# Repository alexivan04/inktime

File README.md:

# InkTime – Open Source Smartwatch Hardware Project

## Overview
InkTime is an open-source, low-cost smartwatch hardware platform designed for mass production.  
This repository contains the complete hardware, manufacturing, and mechanical design files for the device.

The project includes:
- electronic schematic and PCB layout
- manufacturing outputs (Gerber, BOM, Pick & Place)
- complete 3D mechanical assembly
- documentation and design decisions
- validation and review updates

## Repository Structure

```text
InkTime/
│
├── Hardware/
│   ├── inktime.sch
│   ├── inktime.brd
│   └── schematic.pdf
│
├── Manufacturing/
│   ├── gerbers.zip
│   ├── bom.csv
│   └── pick_and_place.csv
│
├── Mechanical/
│   ├── inktime_assembly.step
│   └── inktime_assembly.f3d
│
├── Images/
│   ├── pcb_top.png
│   ├── pcb_bottom.png
│   ├── render_front.png
│   └── exploded_view.png
│
├── LICENSE
└── README.md
````

---

## Block Diagram

```text
Battery
   │
   ▼
Power Management (charger + regulation)
   │
   ▼
nRF52840 Microcontroller
   ├── IMU Sensor (I2C / SPI)
   ├── E-paper Display (SPI)
   ├── Buttons (GPIO)
   ├── USB-C Interface
   ├── Vibration Motor / Shaker
   └── Debug / Test Pads
```

---

## Hardware Architecture

The smartwatch is built around the **nRF52840** microcontroller, selected for:

* low power consumption
* integrated BLE support
* sufficient GPIO availability
* embedded ARM Cortex-M4 core

### Main Modules

* **Microcontroller:** nRF52840
* **Display:** e-paper display connected via SPI
* **Motion Sensor:** IMU connected via I2C/SPI
* **Power Supply:** Li-Po battery with charging IC and voltage regulation
* **User Input:** 3 push buttons
* **Feedback:** vibration motor (shaker)
* **Communication:** USB-C + BLE
* **Programming/Test:** dedicated test pads

---

## PCB Design Notes

### Stack-up

* **4-layer PCB**
* components placed **TOP layer only**
* routing on both TOP and BOTTOM
* GND planes on 1 and 3 layers

### Routing Rules

* power traces: **0.30 mm**
* signal traces: **minimum 0.15 mm**
* no right-angle routing
* minimized vias on power lines
* decoupling capacitors placed near IC supply pins

### RF Requirements

* antenna positioned at PCB edge
* no copper under antenna
* no signal traces below antenna
* board cutout included below antenna region

---

## Mechanical Integration

The PCB is designed to fit inside the provided smartwatch enclosure.

## Design Decisions / Notes

* accepted minor dimension warnings for button and USB alignment per project instructions
* battery connected directly to test pads to save internal volume
* all decoupling capacitors placed as close as possible to supply pins
* RF section isolated with stitched ground vias

---

## License

This project is released under the **Apache 2.0 License**.

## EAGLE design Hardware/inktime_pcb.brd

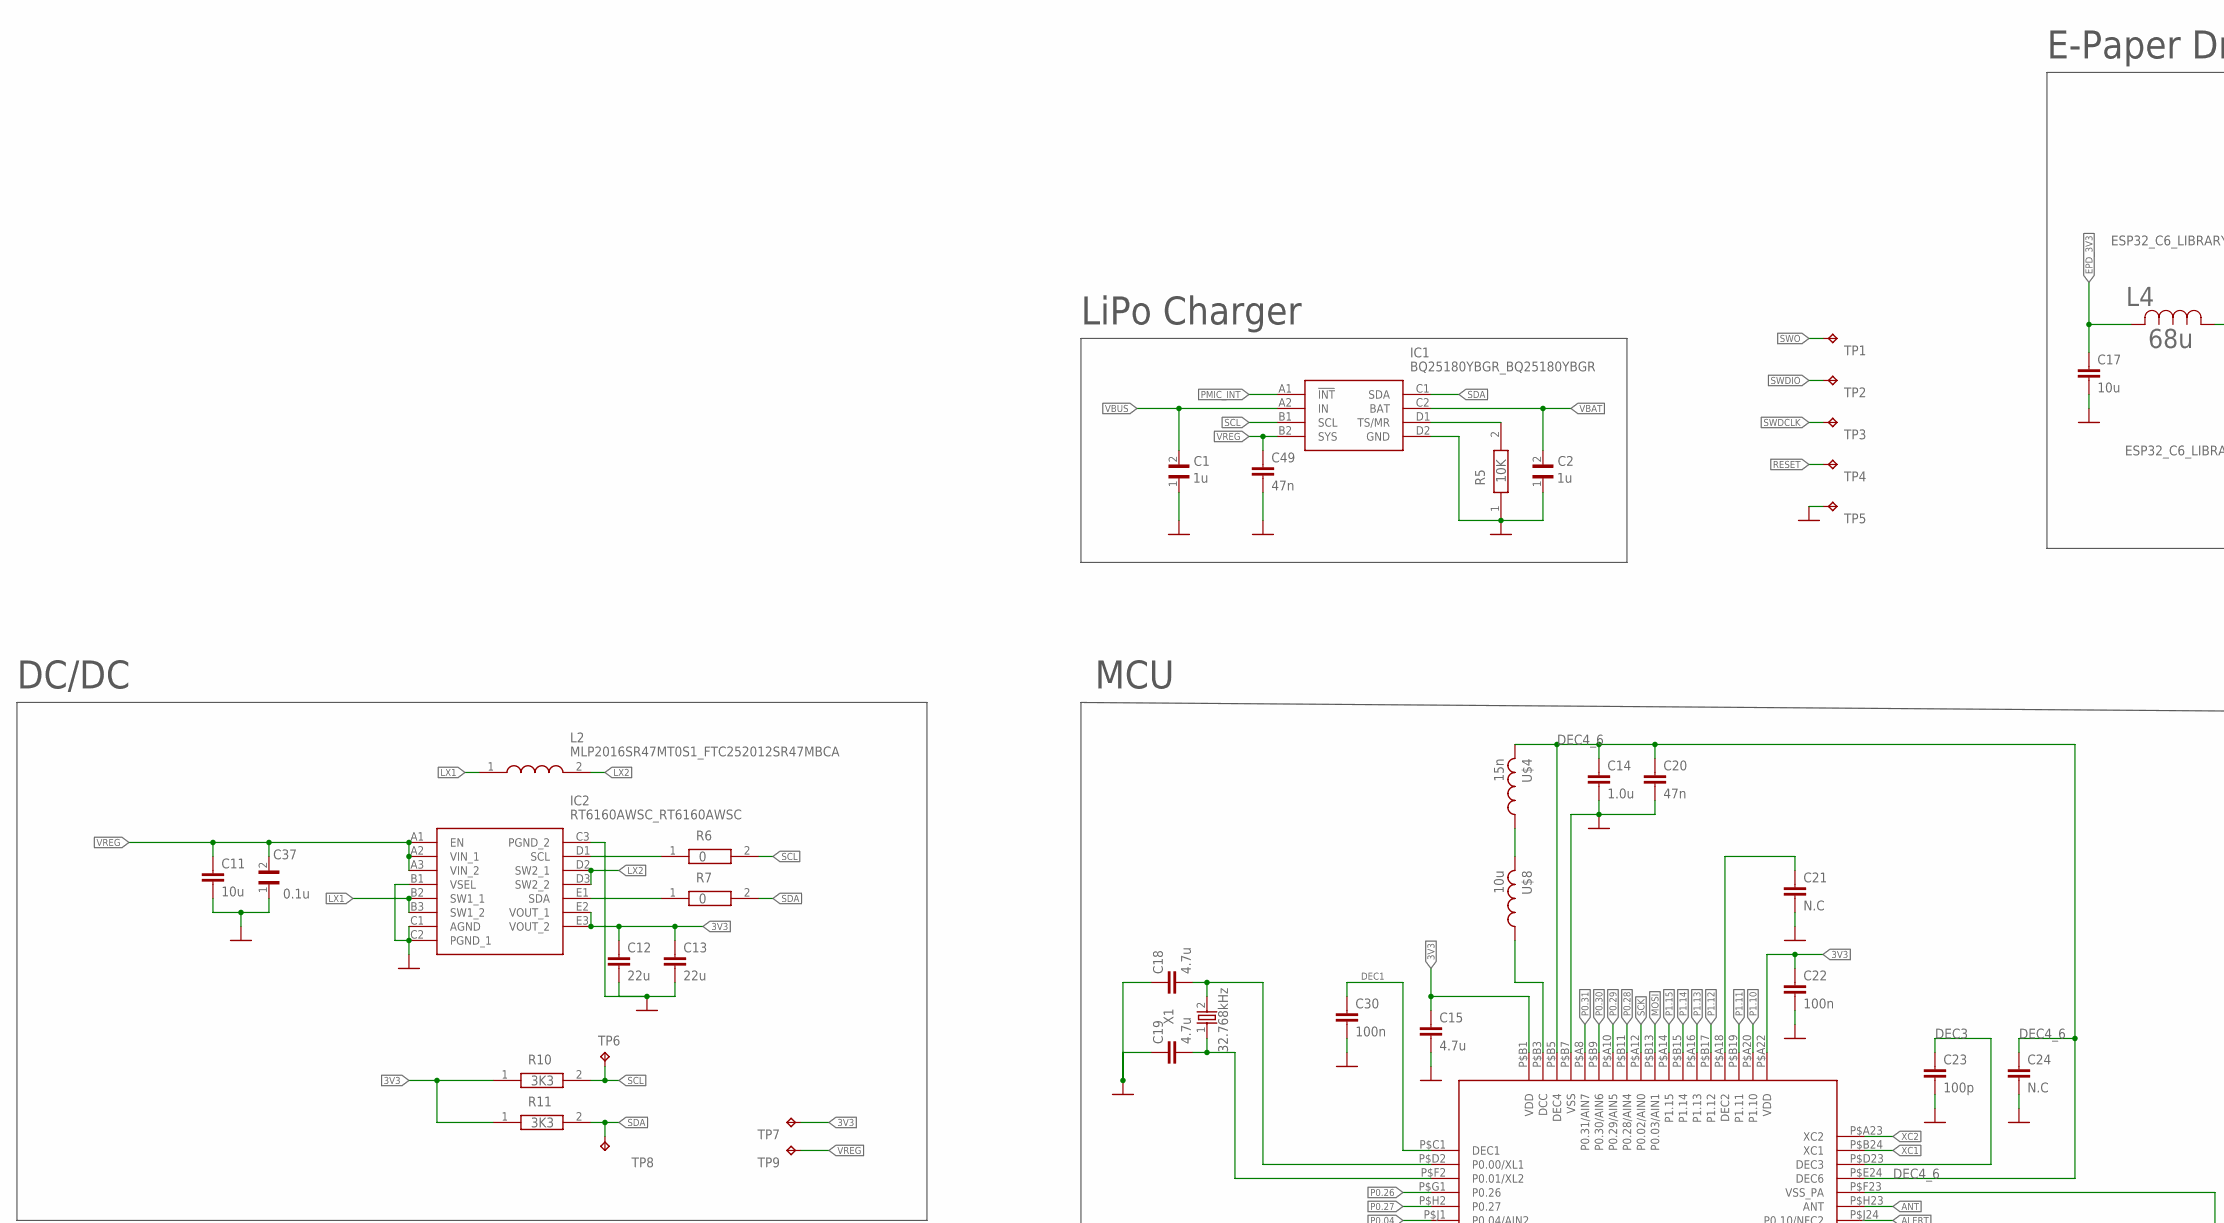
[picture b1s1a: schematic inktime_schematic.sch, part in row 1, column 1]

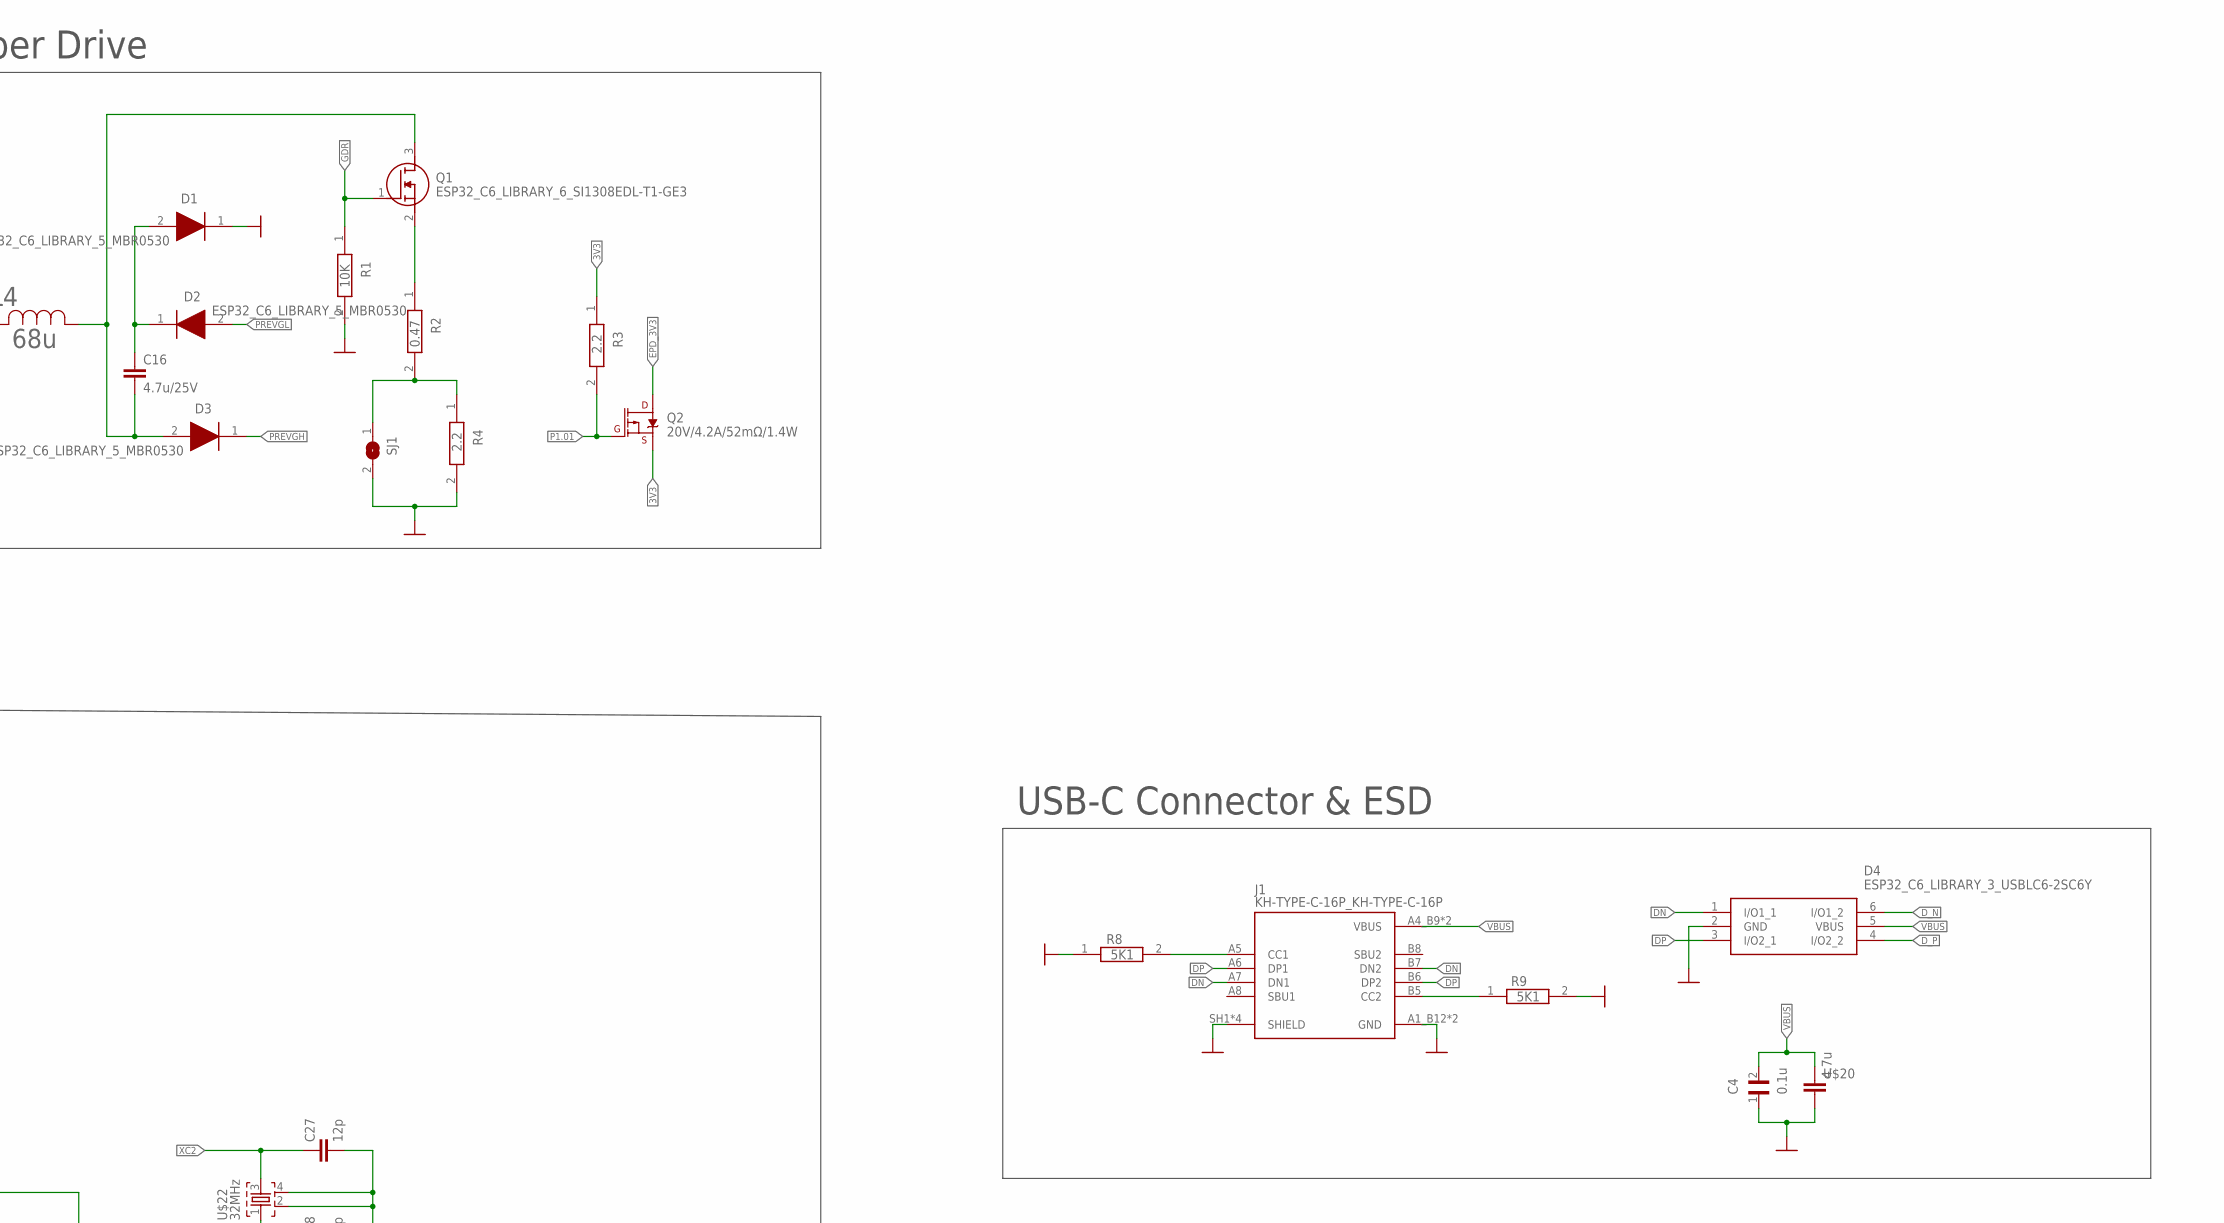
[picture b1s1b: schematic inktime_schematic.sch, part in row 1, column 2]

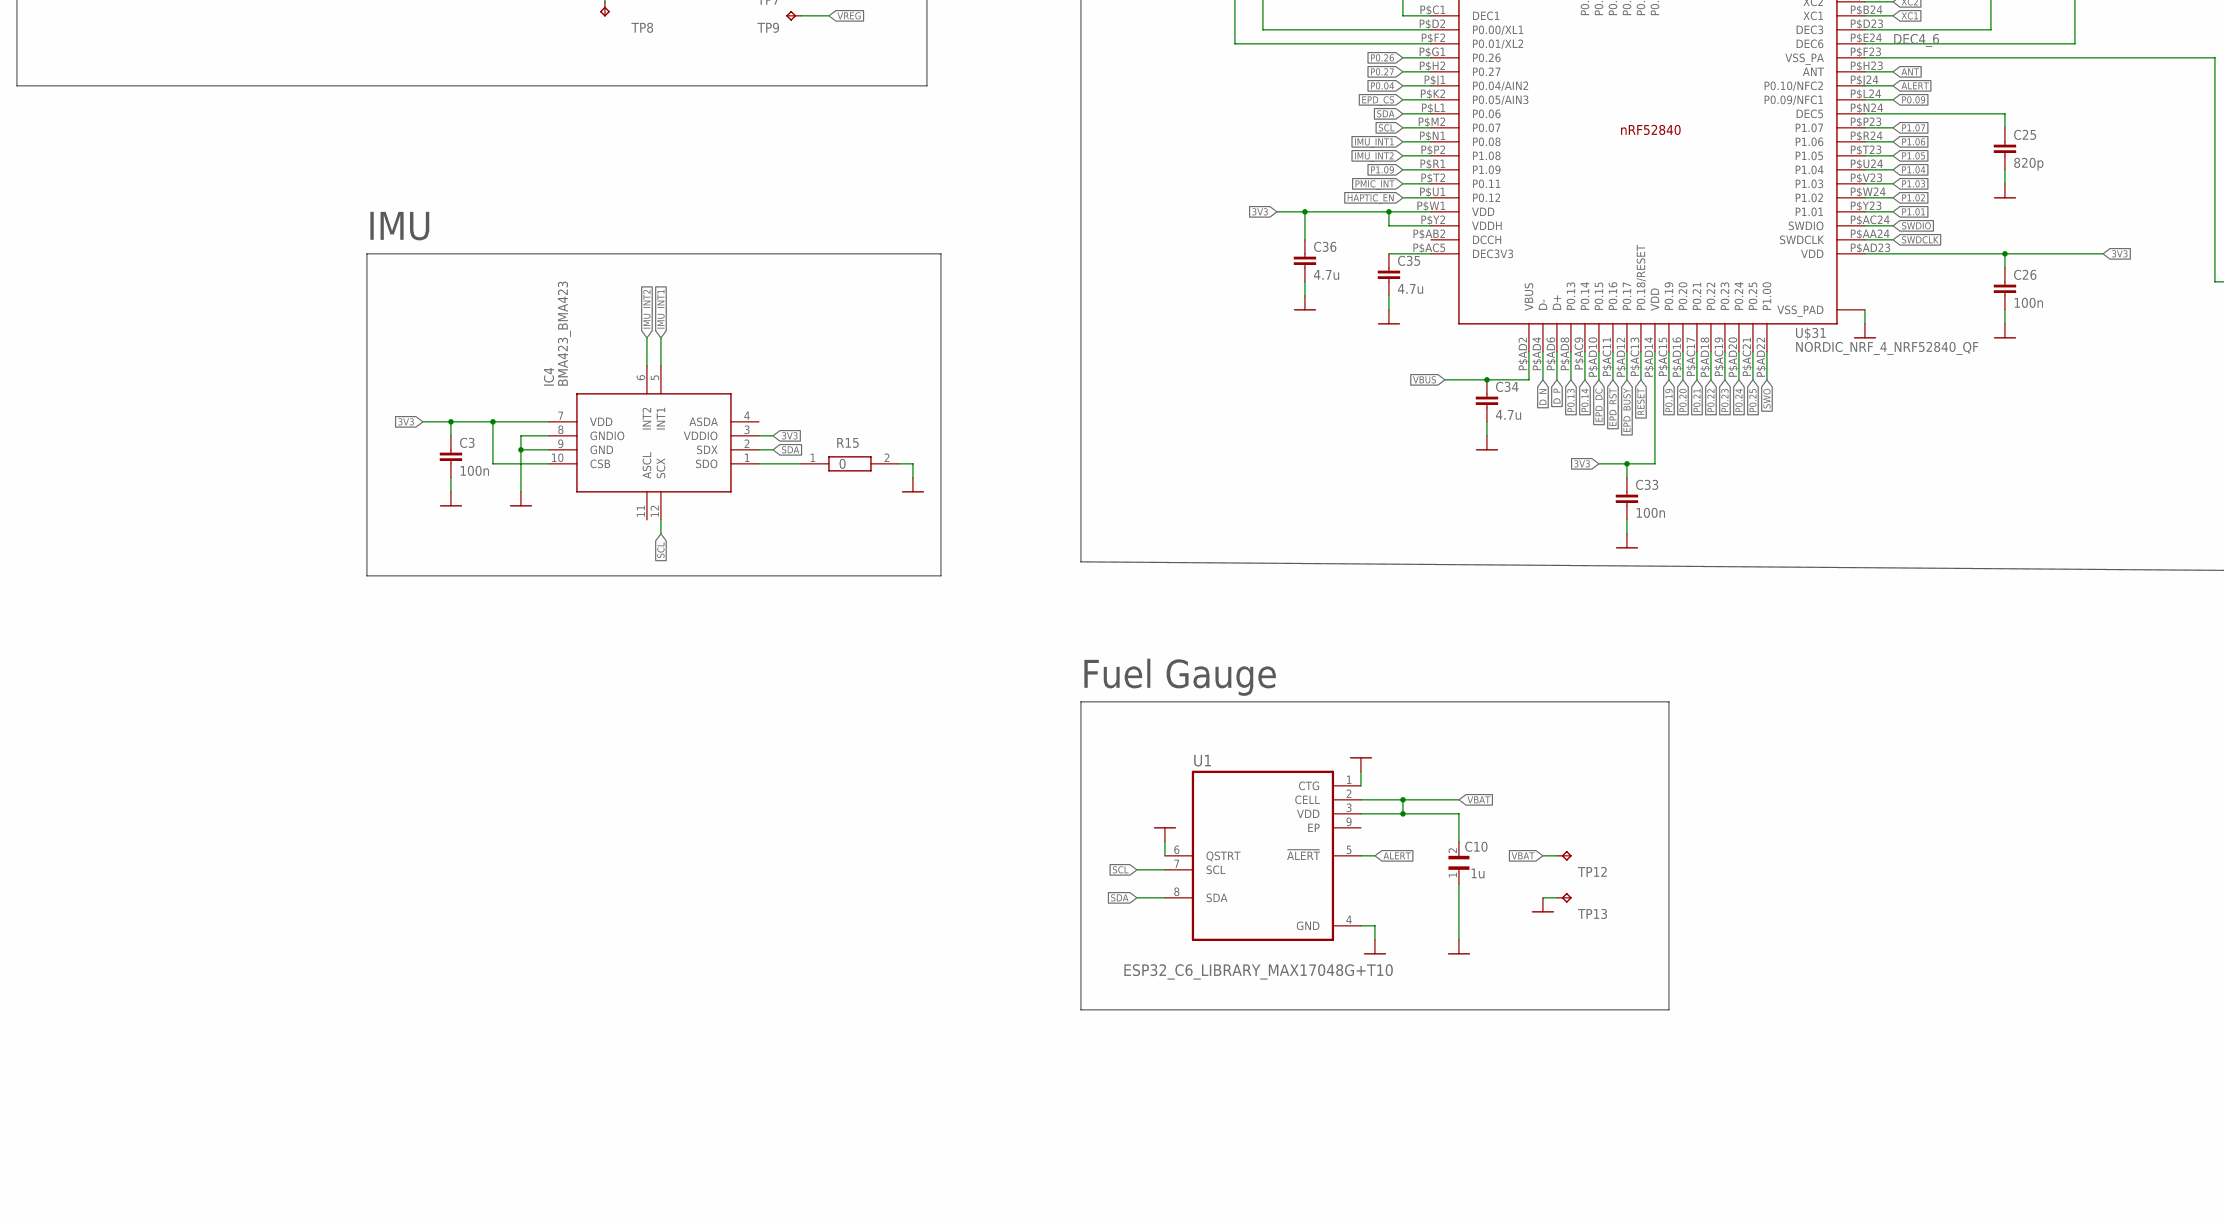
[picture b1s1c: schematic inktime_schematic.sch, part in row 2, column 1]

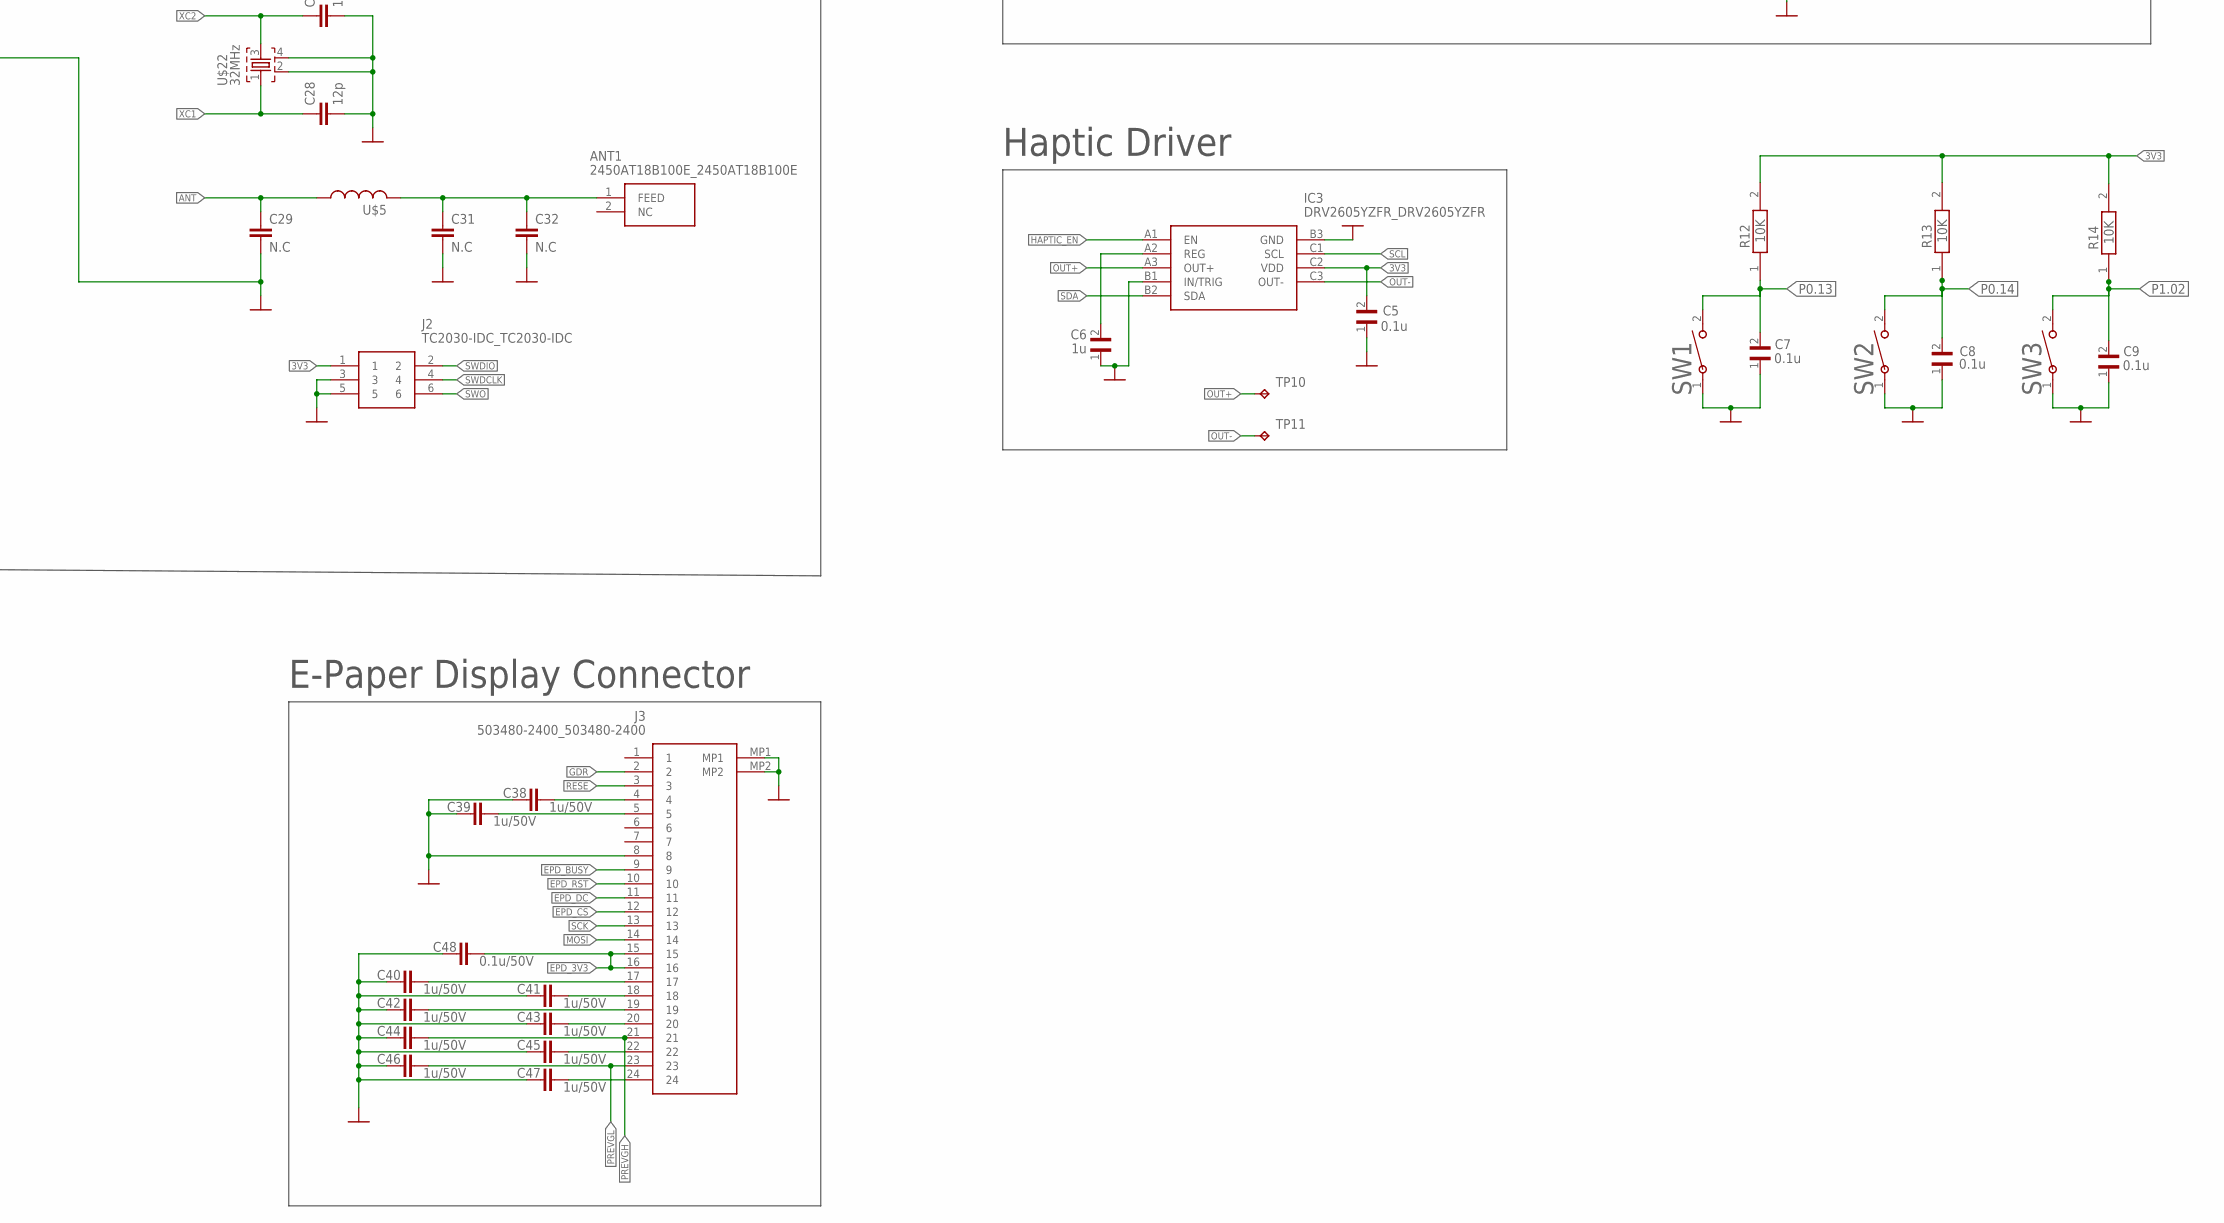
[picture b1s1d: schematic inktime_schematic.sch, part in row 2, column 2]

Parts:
ANT1: 2450AT18B100E_2450AT18B100E; 2450AT18B100E_ANTC3216X140N
C1, C2, C6, C10: 1u; GRM011R60J152KE01L_2_CAPC0201X13N
C3, C22, C26, C30, C33: 100n; NORDIC_NRF_3_RESC0201_L
C4, C5, C7, C8, C9, C37: 0.1u; GRM011R60J152KE01L_2_CAPC0201X13N
C11, C17: 10u; ESP32_C6_LIBRARY_1_ESP32_WROVER_EAGLE-LTSPICE_C0402
C12, C13: 22u; ESP32_C6_LIBRARY_1_ESP32_WROVER_EAGLE-LTSPICE_C0402
C14: 1.0u; ESP32_C6_LIBRARY_1_ESP32_WROVER_EAGLE-LTSPICE_C0402
C15: 4.7u; ESP32_C6_LIBRARY_1_ESP32_WROVER_EAGLE-LTSPICE_C0402
C16: 4.7u/25V; ESP32_C6_LIBRARY_1_ESP32_WROVER_EAGLE-LTSPICE_C0402
C18, C19, C34, C35, C36: 4.7u; NORDIC_NRF_3_RESC0201_L
C20, C49: 47n; NORDIC_NRF_3_RESC0201_L
C21, C24, C29, C31, C32: N.C; NORDIC_NRF_3_RESC0201_L
C23: 100p; NORDIC_NRF_3_RESC0201_L
C25: 820p; NORDIC_NRF_3_RESC0201_L
C27, C28: 12p; NORDIC_NRF_3_RESC0201_L
C38, C39, C40, C41, C42, C43, C44, C45, C46, C47: 1u/50V; NORDIC_NRF_3_RESC0201_L
C48: 0.1u/50V; NORDIC_NRF_3_RESC0201_L
D1, D2, D3: ESP32_C6_LIBRARY_5_MBR0530; ESP32_C6_LIBRARY_5_SOD3716X135N
D4: ESP32_C6_LIBRARY_3_USBLC6-2SC6Y; ESP32_C6_LIBRARY_3_SOT95P280X145-6N
IC1: BQ25180YBGR_BQ25180YBGR; BQ25180YBGR_BGA8C40P2X4_100X155X50
IC2: RT6160AWSC_RT6160AWSC; RT6160AWSC_BGA15C40P3X5_140X230X60
IC3: DRV2605YZFR_DRV2605YZFR; DRV2605YZFR_BGA9C50P3X3_144X144X62
IC4: BMA423_BMA423
J1: KH-TYPE-C-16P_KH-TYPE-C-16P; KH-TYPE-C-16P_KINGHELM_KH-TYPE-C-16P
J2: TC2030-IDC_TC2030-IDC; TC2030-IDC_TC2030IDC
J3: 503480-2400_503480-2400; 503480-2400_5034802400
L2: MLP2016SR47MT0S1_FTC252012SR47MBCA; MLP2016SR47MT0S1_INDC2016X100N
L4: 68u; ESP32_C6_LIBRARY_2_IND_4828-WE-TPC_WRE
Q1: ESP32_C6_LIBRARY_6_SI1308EDL-T1-GE3; ESP32_C6_LIBRARY_6_SOT65P210X110-3N
Q2: 20V/4.2A/52mΩ/1.4W; ESP32_C6_LIBRARY_4_ESP32_C6_LIBRARY_4_ESP32_C6_LIBRARY_4_ES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
R1, R5, R12, R13, R14: 10K; ERA-1AEB3401C_0201
R2: 0.47; ERA-1AEB3401C_0201
R3, R4: 2.2; ERA-1AEB3401C_0201
R6, R7, R15: 0; ERA-1AEB3401C_0201
R8, R9: 5K1; ERA-1AEB3401C_0201
R10, R11: 3K3; ERA-1AEB3401C_0201
SJ1: ESP32_C6_LIBRARY_7_JUMPER_SJ
SW1, SW2, SW3: 2025-10-22_07-23-44_LIBRARY_EVP-AKE31ASW_EVP-AKE3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; 2025-10-22_07-23-44_LIBRARY_SW_EVP-AKE31A_PAN
TP1, TP2, TP3, TP4, TP5, TP6, TP7, TP8, TP9, TP10, TP11, TP12, TP13: HECTOR_WATCH_1_TPTP20R; HECTOR_WATCH_1_TP20R
U1: ESP32_C6_LIBRARY_MAX17048G+T10; ESP32_C6_LIBRARY_SON50P200X200X80-9N
U$4: 15n; NORDIC_NRF_2_RESC0402_L
U$5: NORDIC_NRF_2_INDUCTOR_0402_L; NORDIC_NRF_2_RESC0402_L
U$8: 10u; NORDIC_NRF_2_RESC0402_L
U$20: 4.7u; NORDIC_NRF_3_RESC0201_L
U$22: 32MHz; NORDIC_NRF_BT-XTAL_2016_N
U$31: NORDIC_NRF_4_NRF52840_QF; NORDIC_NRF_4_AQFN50P700X700X85_HS-74N
X1: 32.768kHz; NORDIC_NRF_1_XTAL_3215_N

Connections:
3V1: C35.1, U$31.P$AC5 (DEC3V3)
3V3: C3.1, C5.2, C12.1, C13.1, C15.1, C22.1, C26.1, C33.1, C36.1, IC2.E2 (VOUT_1), IC2.E3 (VOUT_2), IC3.C2 (VDD), IC4.3 (VDDIO), IC4.7 (VDD), IC4.10 (CSB), J2.1, Q2.2 (S), R3.1, R10.1, R11.1, R12.2, R13.2, R14.2, TP7.TP, U$31.P$A22 (VDD), U$31.P$AD14 (VDD), U$31.P$AD23 (VDD), U$31.P$B1 (VDD), U$31.P$W1 (VDD), U$31.P$Y2 (VDDH)
ALERT: U1.5 (!ALERT), U$31.P$J24 (P0.10/NFC2)
ANT: C29.1, U$5.1, U$31.P$H23 (ANT)
DEC1: C30.1, U$31.P$C1 (DEC1)
DEC3: C23.1, U$31.P$D23 (DEC3)
DEC4_6: C14.1, C20.1, C24.1, U$4.2, U$31.P$B5 (DEC4), U$31.P$E24 (DEC6)
DN: D4.1 (I/O1_1), J1.A7 (DN1), J1.B7 (DN2)
DP: D4.3 (I/O2_1), J1.A6 (DP1), J1.B6 (DP2)
D_N: D4.6 (I/O1_2), U$31.P$AD4 (D-)
D_P: D4.4 (I/O2_2), U$31.P$AD6 (D+)
EP: U1.9 (EP)
EPD_3V3: C17.1, C48.2, J3.15, J3.16, L4.2, Q2.3 (D)
EPD_BUSY: J3.9, U$31.P$AD12 (P0.17)
EPD_CS: J3.12, U$31.P$K2 (P0.05/AIN3)
EPD_DC: J3.11, U$31.P$AD10 (P0.15)
EPD_RST: J3.10, U$31.P$AC11 (P0.16)
GDR: J3.2, Q1.1 (G), R1.1
GND: C1.1, C2.1, C3.2, C4.1, C5.1, C6.1, C7.1, C8.1, C9.1, C10.1, C11.2, C12.2, C13.2, C14.2, C15.2, C17.2, C18.1, C19.1, C20.2, C21.2, C22.2, C23.2, C24.2, C25.2, C26.2, C27.2, C28.2, C29.2, C30.2, C31.2, C32.2, C33.2, C34.2, C35.2, C36.2, C37.1, C38.1, C39.1, C40.1, C41.1, C42.1, C43.1, C44.1, C45.1, C46.1, C47.1, C48.1, C49.2, D1.1 (K), D4.2 (GND), IC1.D2 (GND), IC2.B1 (VSEL), IC2.C1 (AGND), IC2.C2 (PGND_1), IC2.C3 (PGND_2), IC3.B1 (IN/TRIG), IC3.B3 (GND), IC4.8 (GNDIO), IC4.9 (GND), J1.A1_B12 (GND), J1.A12_B1 (GND), J1.SH1 (SHIELD), J1.SH2 (SHIELD), J1.SH3 (SHIELD), J1.SH4 (SHIELD), J2.3, J2.5, J3.8, J3.MP1, J3.MP2, R1.2, R4.2, R5.1, R8.1, R9.2, R15.2, SJ1.2, SW1.1, SW2.1, SW3.1, TP5.TP, TP13.TP, U1.1 (CTG), U1.4 (GND), U1.6 (QSTRT), U$20.2, U$22.2, U$22.4, U$31.P$74 (VSS_PAD), U$31.P$75 (VSS_PAD), U$31.P$76 (VSS_PAD), U$31.P$77 (VSS_PAD), U$31.P$78 (VSS_PAD), U$31.P$79 (VSS_PAD), U$31.P$80 (VSS_PAD), U$31.P$81 (VSS_PAD), U$31.P$82 (VSS_PAD), U$31.P$83 (VSS_PAD), U$31.P$84 (VSS_PAD), U$31.P$85 (VSS_PAD), U$31.P$86 (VSS_PAD), U$31.P$87 (VSS_PAD), U$31.P$88 (VSS_PAD), U$31.P$89 (VSS_PAD), U$31.P$90 (VSS_PAD), U$31.P$B7 (VSS), U$31.P$F23 (VSS_PA)
HAPTIC_EN: IC3.A1 (EN), U$31.P$U1 (P0.12)
IMU_INT1: IC4.5 (INT1), U$31.P$N1 (P0.08)
IMU_INT2: IC4.6 (INT2), U$31.P$P2 (P1.08)
LX1: IC2.B2 (SW1_1), IC2.B3 (SW1_2), L2.1
LX2: IC2.D2 (SW2_1), IC2.D3 (SW2_2), L2.2
MOSI: J3.14, U$31.P$B13 (P0.03/AIN1)
unnamed: C18.2, U$31.P$D2 (P0.00/XL1), X1.2
unnamed: C19.2, U$31.P$F2 (P0.01/XL2), X1.1
unnamed: U$4.1, U$8.2
unnamed: U$8.1, U$31.P$B3 (DCC)
unnamed: C25.1, U$31.P$N24 (DEC5)
unnamed: IC1.D1 (TS/MR), R5.2
unnamed: ANT1.1 (FEED), C31.1, C32.1, U$5.2
unnamed: C21.1, U$31.P$A18 (DEC2)
unnamed: IC2.D1 (SCL), R6.1
unnamed: IC2.E1 (SDA), R7.1
unnamed: C6.2, IC3.A2 (REG)
unnamed: J1.A5 (CC1), R8.2
unnamed: J1.B5 (CC2), R9.1
unnamed: Q1.2 (S), R2.1
unnamed: IC4.1 (SDO), R15.1
unnamed: C38.2, J3.4
unnamed: C39.2, J3.5
unnamed: R2.2, R4.1, SJ1.1
unnamed: C16.1, D1.2 (A), D2.1 (K)
unnamed: C16.2, D3.2 (A), L4.1, Q1.3 (D)
unnamed: C40.2, J3.17
unnamed: C41.2, J3.18
unnamed: C42.2, J3.19
unnamed: C43.2, J3.20
unnamed: C45.2, J3.22
unnamed: C47.2, J3.24
OUT+: IC3.A3 (OUT+), TP10.TP
OUT-: IC3.C3 (OUT-), TP11.TP
P0.04: U$31.P$J1 (P0.04/AIN2)
P0.09: U$31.P$L24 (P0.09/NFC1)
P0.13: C7.2, R12.1, SW1.2, U$31.P$AD8 (P0.13)
P0.14: C8.2, R13.1, SW2.2, U$31.P$AC9 (P0.14)
P0.19: U$31.P$AC15 (P0.19)
P0.20: U$31.P$AD16 (P0.20)
P0.21: U$31.P$AC17 (P0.21)
P0.22: U$31.P$AD18 (P0.22)
P0.23: U$31.P$AC19 (P0.23)
P0.24: U$31.P$AD20 (P0.24)
P0.25: U$31.P$AC21 (P0.25)
P0.26: U$31.P$G1 (P0.26)
P0.27: U$31.P$H2 (P0.27)
P0.28: U$31.P$B11 (P0.28/AIN4)
P0.29: U$31.P$A10 (P0.29/AIN5)
P0.30: U$31.P$B9 (P0.30/AIN6)
P0.31: U$31.P$A8 (P0.31/AIN7)
P1.01: Q2.1 (G), R3.2, U$31.P$Y23 (P1.01)
P1.02: C9.2, R14.1, SW3.2, U$31.P$W24 (P1.02)
P1.03: U$31.P$V23 (P1.03)
P1.04: U$31.P$U24 (P1.04)
P1.05: U$31.P$T23 (P1.05)
P1.06: U$31.P$R24 (P1.06)
P1.07: U$31.P$P23 (P1.07)
P1.09: U$31.P$R1 (P1.09)
P1.10: U$31.P$A20 (P1.10)
P1.11: U$31.P$B19 (P1.11)
P1.12: U$31.P$B17 (P1.12)
P1.13: U$31.P$A16 (P1.13)
P1.14: U$31.P$B15 (P1.14)
P1.15: U$31.P$A14 (P1.15)
PMIC_INT: IC1.A1 (!INT), U$31.P$T2 (P0.11)
PREVGH: C44.2, D3.1 (K), J3.21
PREVGL: C46.2, D2.2 (A), J3.23
RESE: J3.3
RESET: TP4.TP, U$31.P$AC13 (P0.18/RESET)
SCK: J3.13, U$31.P$A12 (P0.02/AIN0)
SCL: IC1.B1 (SCL), IC3.C1 (SCL), IC4.12 (SCX), R6.2, R10.2, TP6.TP, U1.7 (SCL), U$31.P$M2 (P0.07)
SDA: IC1.C1 (SDA), IC3.B2 (SDA), IC4.2 (SDX), R7.2, R11.2, TP8.TP, U1.8 (SDA), U$31.P$L1 (P0.06)
SWDCLK: J2.4, TP3.TP, U$31.P$AA24 (SWDCLK)
SWDIO: J2.2, TP2.TP, U$31.P$AC24 (SWDIO)
SWO: J2.6, TP1.TP, U$31.P$AD22 (P1.00)
VBAT: C2.2, C10.2, IC1.C2 (BAT), TP12.TP, U1.2 (CELL), U1.3 (VDD)
VBUS: C1.2, C4.2, C34.1, D4.5 (VBUS), IC1.A2 (IN), J1.A4_B9 (VBUS), J1.A9_B4 (VBUS), U$20.1, U$31.P$AD2 (VBUS)
VREG: C11.1, C37.2, C49.1, IC1.B2 (SYS), IC2.A1 (EN), IC2.A2 (VIN_1), IC2.A3 (VIN_2), TP9.TP
XC1: C28.1, U$22.1, U$31.P$B24 (XC1)
XC2: C27.1, U$22.3, U$31.P$A23 (XC2)

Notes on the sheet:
LiPo Charger
DC/DC
MCU
IMU
Fuel Gauge
E-Paper Display Connector
USB-C Connector & ESD
Haptic Driver
E-Paper Drive

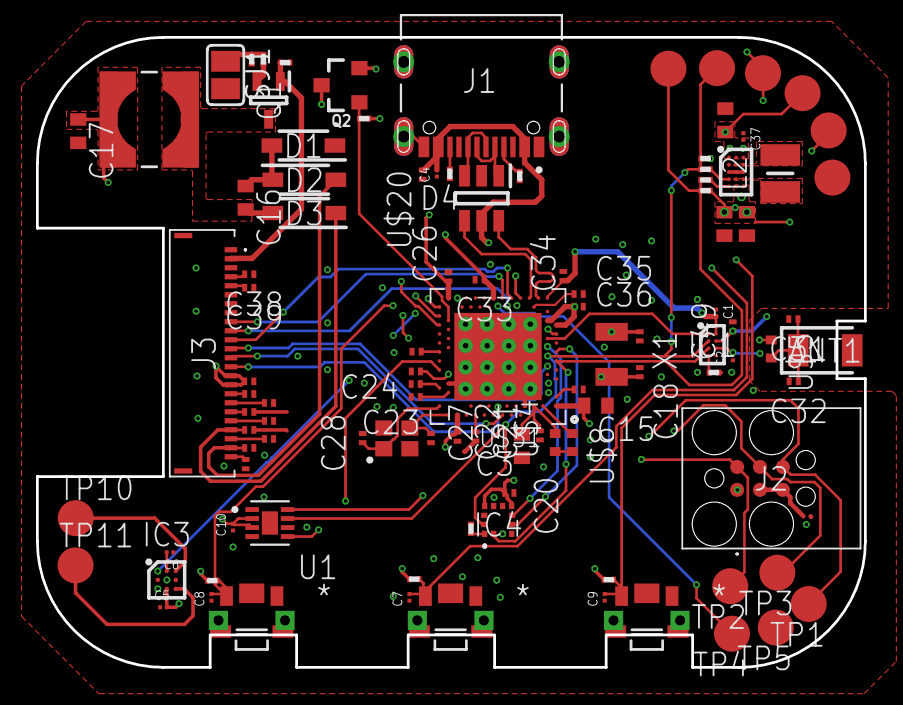
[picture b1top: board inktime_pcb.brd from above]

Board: 4 copper layers, 46.0 x 35.0 mm, 105 parts (0 on the bottom side), 71 nets.

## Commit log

2026-03-10 mock readme
2026-04-10 added schematic and base PCB
2026-04-21 final version
2026-04-21 readme changed
2026-04-21 readme modified
2026-04-21 clean up README formatting
    Removed unnecessary markdown formatting from the README.
2026-04-21 3d files
2026-04-21 added assembly image
2026-04-21 removed cable
2026-04-21 more edits
2026-04-21 added images

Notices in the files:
parts and their libraries:
COPYRIGHT: Copyright (C) 2025 Ultra Librarian. All rights reserved.
COPYRIGHT: Copyright (C) 2024 Ultra Librarian. All rights reserved.
